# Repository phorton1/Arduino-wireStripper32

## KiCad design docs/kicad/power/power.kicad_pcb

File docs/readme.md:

# wireStripper32 - Compact breadboard Wire Cutter and Stripper

**Home** --
**[Design](design.md)** --
**[Electronics](electronics.md)** --
**[Build](build.md)** --
**[Firmware](firmware.md)** --

I wanted to build a wire stripper to cut 22 guage solid core breadboard wire.
After a review of existing projects on YouTube and the web, I decided to
design my own.

- **Compact** - This design is very compact.  The wire cutter does not take
  up a lot of room on my desk or work surface.
- **Web UI** - There is no built in touch screen.  This saves on component
  costs and design complexity, by taking advantage of the ESP32's **wifi**
  capabilities to provide a *Web User Interface* that can be accessed from
  a cell phone or any other device with a browser on the LAN
- **Infrared Wire Sensor** - allows for easy **Loading** and **Unloading** of wire.
- **Single Button** - in addition to the *Web UI* there is a single
  button that can **Stop** the machine and **Unload or Load** the wire.
- **Common Tool** - the machine uses a commonly available inexpensive
  manual wire cutter.
- **Standard 12V Power Supply** - the machine uses a commonly available
  standard 2.5A 12V power supply and has an **On/Off** switch.

## Documentation Outline

The following pages of documentation are intended to as a *tutorial* for
a **maker** who is *building* this wire cutter/stripper:

- **[Design](design.md)** - An overview of the **requirements** and **design** of the machine
- **[Electronics](electronics.md)** - **Schematics**, **PCB layouts**, and **Cabling** details
- **[Build](build.md)** - **Building* the wireStripper
- **[Firmware](firmware.md)** - Compiling and installing the **Firmware** to the ESP32

## Files Available in this repository

This machine was *designed* using the **Fusion 360** CAD program and
the [**KiCAD**](https://www.kicad.org/) schematic and PCB design program.
The main outputs from Fusion 360 are the **STL Files** (3D models) used to
3D print the plastic parts.

The outputs from *KiCad* include the basic **schematic**, and
the **Gerber** and **Excellon** files used to make the PCBs.
The program [**FlatCAM**](https://bitbucket.org/jpcgt/flatcam/downloads/)
was used to generate the GCODE files from those files for running my
[**cnc3018**](https://github.com/phorton1/Arduino-esp32_cnc3018)
to **mill, epoxy coat, drill, and cut out** the PCBs (printed circuit boards).

The following sub-folders and their children can be found within this 'docs' folder

- [**fusion**](https://github.com/phorton1/Arduino-wireStripper32/tree/master/docs/fusion) -
   contains the final output *STL* files and *Fusion 360* design that produces them.
- [**kicad**](https://github.com/phorton1/Arduino-wireStripper32/tree/master/docs/kicad) -
  contains the **kiCAD** project, electronics schematics, and PCB design files
- [**prusa**](https://github.com/phorton1/Arduino-wireStripper32/tree/master/docs/kicad) -
  contains *projects* and *gcode* for printing the 3D plastic parts on a **Prusa MK3s** printer.

## Please Also See

This project directly makes direct use of my
[**MyIOT**](https://github.com/phorton1/Arduino-libraries-myIOT)
("my internet of things*) repository, which provides a generalized approach to
building relatively simple parameter driven ESP32 devices that include a Web UI.

The PCBs (printed circuit boards) were **milled** using the
[**cnc3018**](https://github.com/phorton1/Arduino-esp32_cnc3018) CNC
machine that I built.

I hope you will take a few minutes to check out some of these other pages too!!

## Credits

This project directly relies upon the public open source Arduino development system,
the Espressif ESP32 online documentation and additions to the Arduino IDE, as
well as a number open source Arduino libraries

I would like to thank the countless individuals who have contributed to making these
development tools, source codes, and documentation available for free public use, including,
but not limited to:

- [KiCad](https://www.kicad.org/)
- [FlatCAM](https://bitbucket.org/jpcgt/flatcam/downloads/) by **Juan Pablo Caram**
- [Arduino IDE and Libraries](https://www.arduino.cc/)
- [Espressif Systems](https://www.espressif.com/en/products/socs/esp32)
- [Adafruit NeoPixel Library](https://github.com/adafruit/Adafruit_NeoPixel)

## License

This program, project, and repository is free software: you can redistribute it and/or modify
it under the terms of the GNU General Public License Version 3 as published by
the Free Software Foundation.

These materials are distributed in the hope that they will be useful,
but WITHOUT ANY WARRANTY; without even the implied warranty of
MERCHANTABILITY or FITNESS FOR ANY PARTICULAR PURPOSE.  See the
GNU General Public License for more details.

Please see [LICENSE.TXT](../LICENSE.TXT) for more information.

**Next:** A [**Design Overview**](design.md) of the clock ...

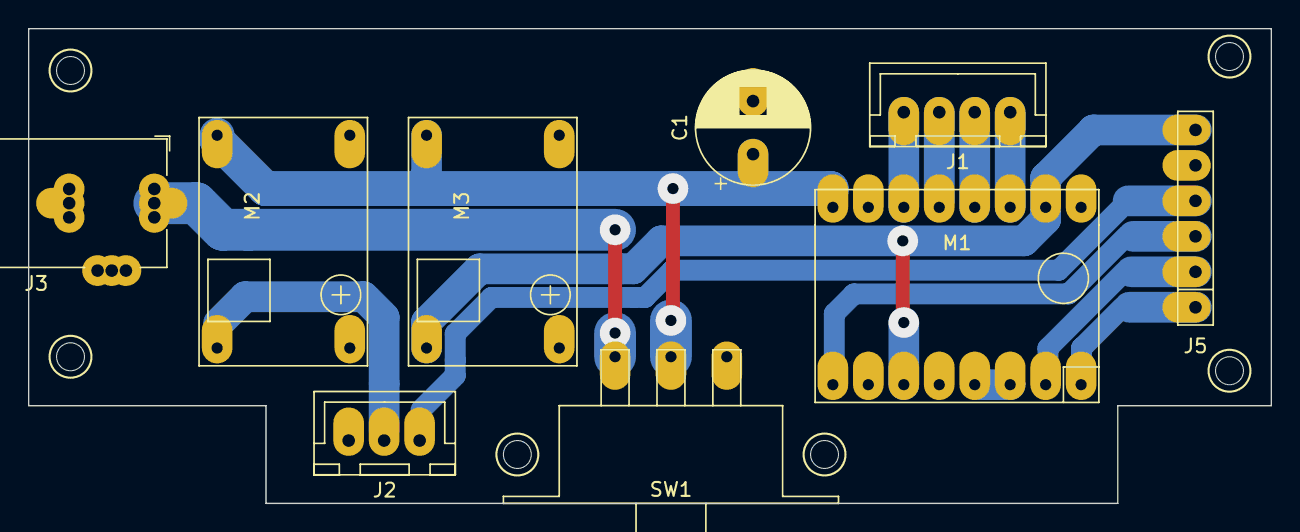
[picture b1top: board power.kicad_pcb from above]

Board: 2 copper layers, 89.0 x 34.0 mm, 9 parts (0 on the bottom side), 14 nets.

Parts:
C1: 100uf; CP_my100uf
J1: EXTRUDER; JST4
J2: CUTTER; JST3
J3: 12V_IN; myBarrelJack
J5: POWER; myPinSocket_1x06
M1: A4988; a498
M2: BUCK2; buck-mini360
M3: BUCK1; buck-mini360
SW1: ON_OFF; slide_switch_big_right

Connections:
+5V: J5.6, M1.6, M1.15, M3.3
+12V: C1.1, M1.9, M2.4, M3.4, SW1.2
EXT_DIR: J5.1, M1.1
EXT_EN: J5.3, M1.8
EXT_STEP: J5.2, M1.2
GND: C1.2, J2.3, J3.2, J5.5, M1.10, M1.16, M2.1, M2.2, M3.1, M3.2
unnamed: J1.1, M1.14
unnamed: J1.2, M1.13
unnamed: J1.3, M1.12
unnamed: J1.4, M1.11
unnamed: J3.1, SW1.3
unnamed: M1.3, M1.4
SERVO: J2.1, J5.4
SERVO_POWER: J2.2, M2.3

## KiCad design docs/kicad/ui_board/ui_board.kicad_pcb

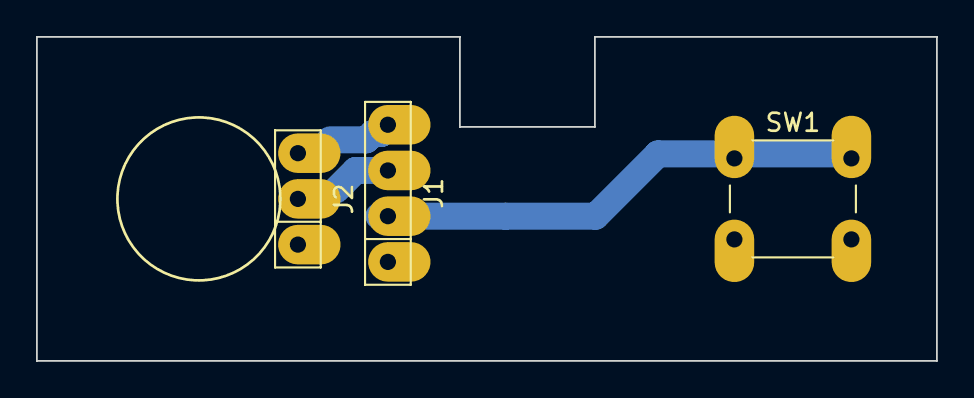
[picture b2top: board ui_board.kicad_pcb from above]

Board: 2 copper layers, 50.0 x 18.0 mm, 3 parts (0 on the bottom side), 4 nets.

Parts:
J1: UI; my4pin
J2: LED; my3pin
SW1: BUTTON; SW_PUSH_6mm_H8mm

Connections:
+3V3: J1.4, J2.3
BUTTON: J1.2, SW1.1
GND: J1.1, J2.1, SW1.2
LED: J1.3, J2.2

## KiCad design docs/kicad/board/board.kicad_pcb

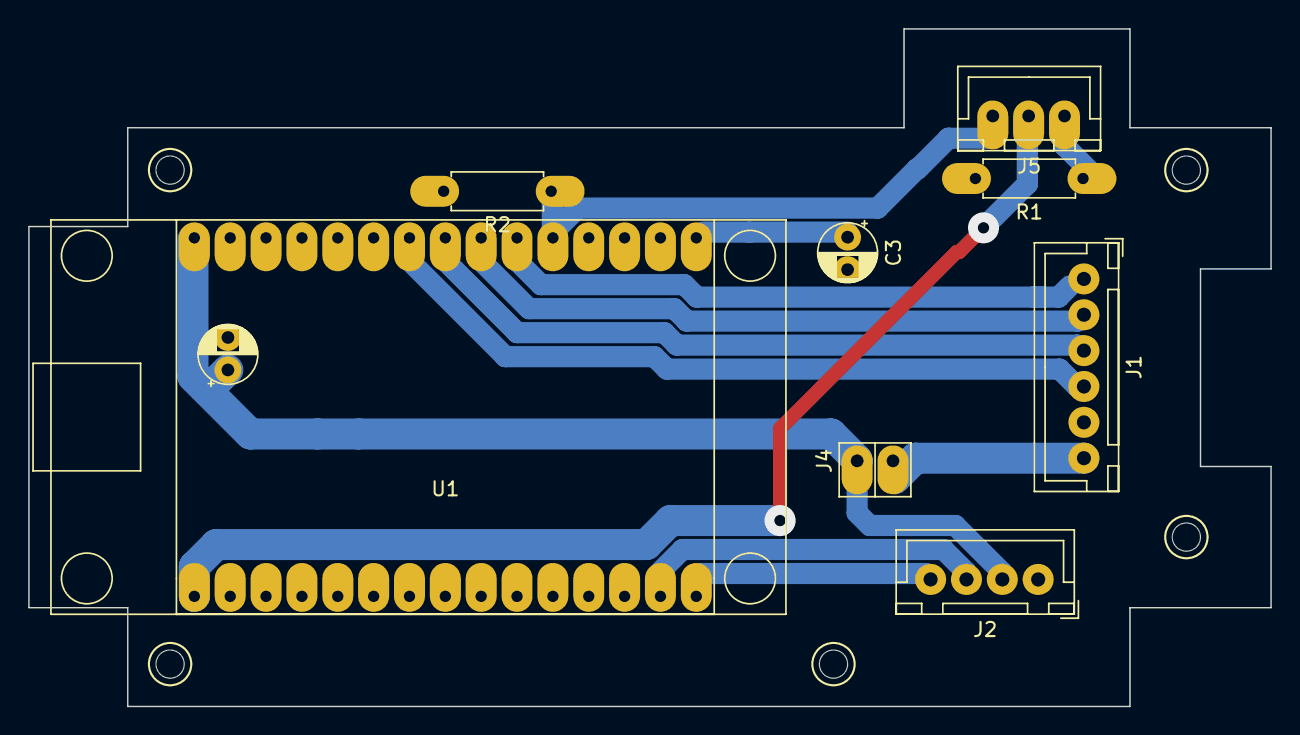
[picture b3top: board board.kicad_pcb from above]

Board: 2 copper layers, 88.0 x 48.0 mm, 9 parts (0 on the bottom side), 13 nets.

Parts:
C2: 100uf; CP_my10uf
C3: 10uF; CP_my10uf
J1: POWER; myJSTx06
J2: UI; myJSTx04
J4: 5V Jumper; pinHeader1x2
J5: IR_SENSOR; JST3
R1: 220; resistor
R2: 1K; resistor
U1: ESP32_DEV_0; esp32_dev_0

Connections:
+3V3: J5.2, U1.30
+5V: J1.6, J4.2
BTN: J2.3, U1.17
EXT_DIR: J1.2, U1.9
EXT_EN: J1.1, U1.10
EXT_STEP: J1.3, U1.8
GND: C2.2, C3.2, J1.5, J2.1, R1.2, R2.2, U1.2, U1.29
IR_SENSE: J5.3, R2.1, U1.11
LED: J2.4, U1.16
unnamed: C3.1, U1.15
unnamed: J5.1, R1.1
SERVO: J1.4, U1.7
VIN: C2.1, J2.2, J4.1, U1.1

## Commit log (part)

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2024-07-24 initial commit new repo
2024-07-24 added myIOT 'data' submodule
2024-07-24 LICENSE.TXT and initial docs
2024-07-24 a couple of initial doc images
2024-07-25 added MOVE command
2024-07-27 Docs mostly - intallable bin image - minor changes to board pcbs for presentation
2024-09-21 submodule(data) auto_commit(83767cf1) Added a Widget tab to the main myIOT webpage; added jqplot CSS and JS files; wrote iotPlot.js prototype of charting within a "widget" - see fridgeController chec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
2024-09-22 submodule(data) auto_commit(0465efe4) myIOT Widets II - introduce basic HTTP caching; refactor myIOT iotPlot.js into iotCommon.js, cleanup Widget concepts and code; sanity checkcin
2024-09-22 submodule(data) auto_commit(e76456cf) iotPlot.js - minor change to Fix Zooming; otherwise "comments only"
2024-09-24 submodule(data) auto_commit(86b02898) created a WS based Plotter!
2024-09-25 submodule(data) auto_commit(331f60b7) refined myIOT plotter with LEGENDS and using device specific PLOT_TYPES if available; theClock3 implementation of PLOT_CYCLES and PLOT_WAVES
2024-09-25 submodule(data) auto_commit(18ec6f60) iotPlot.js - missing ctx.lineWidth = 1; for plot itself
2024-09-26 submodule(data) auto_commit(68039dc2) prep for bilgeAlarm bar chart widget - reworked myIOTDataLog to send records from back of file until dt stamp is met, which required myIOTWebServer to use HTTP 1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
2024-09-29 submodule(data) auto_commit(416ed000) added prototype bilgeAlarm jqPlot Widget using added "alt_data_format" and custom chart_header and chart_data code in onCustomLink(). modified myIOT/data index.h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
2024-10-01 submodule(data) auto_commit(2407a228) added global DEGREE_TYPE and VALUE_STYLE_TEMPERATURE, supprted in webUI, dataLog, and Charts
2024-10-06 submodule(data) auto_commit(28556b88) iotCommon.js - changed keep_alive timings and const's to vars to allow debugging at runtime
2024-10-07 submodule(data) auto_commit(f3e2065d) reduce size of WS status fields in index.html
2024-10-10 submodule(data) auto_commit(b622c3ba) Use regular javascript alert instead of myAlert and hide progress on upload_error
2024-10-19 submodule(data) auto_commit(c0e7ba5a) add better resizing to iotChart.js
2024-10-21 submodule(data) auto_commit(b811e3f8) move generic uiButtons to myIOTButtons; implement initial tempController uiScreen and PCB board(s)
2024-10-25 submodule(data) auto_commit(fdbad871) fix myIOTServer with new chart stuff (pass uuids, caching, etc)
2025-02-02 reburned ESP32 (usb port broke) setting current new defaults
2025-12-15 submodule(data) auto_commit(b649fc3a) iotChart.js - added scheme for setting device specific series colors
2025-12-18 submodule(data) auto_commit(1adaeb45) reworked iotChart.js incremental update scheme starting with Arduino-boat-drainPump
2025-12-18 submodule(data) auto_commit(b6ac0c88) starting in Arduino-boat-arirco, major rework of iotChart.js and how charts are implemented - use common chart.html instead of specific/extra_data/device_chart.h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
2025-12-18 submodule(data) auto_commit(1efc7b72) rework iotChart.js::determineNumberTicks() starting with drain_pump
2025-12-18 submodule(data) auto_commit(78894e93) change onChartResize() to use create_chart() instead of built in jqplot.replot()
2025-12-18 submodule(data) auto_commit(40916b0c) separate iotChart.js doChart() as init only method from onXXX() UI methods - yet another rework of iotChart.js and myIOTDataLog starting with fridgeController
2025-12-18 submodule(data) auto_commit(b923e44d) back to static html for chart.html; got rid of myIOTDataLog::getChartHtml() starting with tempController
2025-12-18 submodule(data) auto_commit(a4e2ed81) change chart.html and iotChart.js to use and remove style "degree_hidden" for devices that chart things with degrees
2025-12-18 submodule(data) auto_commit(a9754dbc) fixed renamed control _degree_type
2025-12-18 submodule(data) auto_commit(03555741) fix malformed chart.html <select id='_chart_period'> text
2025-12-19 submodule(data) auto_commit(1cb3d61a) add onChartResize() back to chart.html
2025-12-19 submodule(data) auto_commit(253976a9) more changes to iotChart.js starting with tempController so at least refresh works *well* if no zooming involved
2025-12-19 commit parents
2025-12-20 submodule(data) auto_commit(eccd1fcc) iotChart.js - added save/restore of series visibility and refactored code
2025-12-31 submodule(data) auto_commit(2a8db875) add degree_type to myIOT chart_header for use in initializing iotChart.js
2026-02-22 submodule(data) auto_commit(37a6a76c) added framework for chart.html to pass "data_name" to allow multiple charts per device; ALSO store most recent chart period in browser storage
2026-03-04 submodule(data) auto_commit(75bcbcb5) iotChart.js - added smaller (UINT8, CENTIGRADE8, UINT8x10) iotDataLog LOG_TYPES and updated client ctors
2026-03-04 submodule(data) auto_commit(d6f02205) added myIotTempSensor "raw" accessors & used to shrink fridgeController.dataLog file size; got rid of FAKE_COMPRESSOR
2026-03-05 remove forward and lateral references to myIOT "bilgeAlarm" repo
2026-03-05 submodule(data) auto_commit(ecc76888) update myIOT data submodule readme.md to remove forward references to actual implmented device repos
2026-03-07 submodule(data) auto_commit(5dbe3136) Save chart visibility and zorders in locsl storage
2026-04-04 submodule(data) auto_commit(a0279fca) New iotChart tooltips and dataLog record maintenance feature.
2026-04-04 submodule(data) auto_commit(de0689cf) disable Scan/Delete endpoints and just View data records for devices that have graphs, but no SD card
2026-06-28 submodule(data) auto_commit(eadab9ea) added myIOTDataLog type LOG_COL_TYPE_INT16_10 to support volts (fridgeController)
